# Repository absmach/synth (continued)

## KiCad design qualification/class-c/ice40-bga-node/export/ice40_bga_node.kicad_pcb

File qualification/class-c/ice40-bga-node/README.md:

# iCE40HX4K BGA node with a USB-C input and an MCU (Class C, case 1)

An iCE40HX4K FPGA in a 121-ball, 0.8 mm-pitch BGA with its supply chain, an SPI boot flash, one 12-pin header and four status LEDs, powered from a USB-C receptacle, with an STM32F103C8 companion MCU that programs the flash over USB, on six copper layers. It answers #328 under #40: a board with a BGA part, escaped under the pads, with via and fanout rules, made by an agent driving `synth mcp`.

## The board

| Group | Parts |
|---|---|
| Power entry | `J1` Korean Hroparts TYPE-C-31-M-12 USB-C receptacle (5 V from VBUS) with `R_CC1` and `R_CC2`, 5.1 k pull-downs on CC1 and CC2; `F1` Bourns MF-NSMF050-2 (0.5 A hold, 1 A trip, 13.2 V); `D1` Nexperia PTVS6V0S1UR (6.0 V standoff, 6.67 V minimum breakdown, 10.3 V clamp at 38.8 A); `Q1` Vishay SI2301CDS P-MOSFET reverse-polarity stage; `R3`, `C1` |
| USB data | `R25` and `R26`, 22 ohm series resistors in D+ and D- |
| MCU | `U5` STMicroelectronics STM32F103C8T6 (LQFP-48) on `+3V3_MCU`, which comes from `+3V3` through the ferrite bead `FB2`; supply decoupling `C27` to `C32` (five 100 nF and 4.7 uF); reset network `R21`, `C33` and the tactile switch `SW1`; `R22` pulls BOOT0 low; the crystal `Y1` with `C34` and `C35`; the 5-pin SWD header `J4` (3V3, SWDIO, SWCLK, NRST, GND) |
| 3.3 V | `U3` AMS1117-3.3 with 4 x 10 uF |
| 1.2 V core | `U4` Texas Instruments TLV70012DDCR, TSOT-23-5, with 1 uF in and 1 uF + 4.7 uF out; PLL supply `VCCPLL` through the ferrite bead `FB1` (Murata BLM18AG601SN1D) and `C20` to `C22` |
| FPGA | `U1` Lattice iCE40HX4K-BG121 (`VPP_FAST` unconnected), every supply ball decoupled |
| Configuration | `U2` Winbond W25Q128JVSIQ, SOIC-8 208 mil (5.3 mm body), master SPI; `CRESET_B` pulled up, `CDONE` with its LED |
| I/O | `J3` JXTCONN JXT-PZ2.54-1X12P-A1, 12 positions (3.3 V, ground and four FPGA I/O through 100 ohm series resistors) |
| Indicators and test points | four LEDs in one row, test points on 5 V, 3.3 V, 1.2 V, `CDONE` and `CRESET_B`, two M2.5 mounting holes at opposite corners (bottom left and top right) |

The MCU's job is to program the flash. `U5` streams the bitstream from the host over USB to `U2` over SPI1 (`PA4` to `PA7` to the flash's chip select, clock and data pins) and drives `CRESET_B` and `CDONE` from `PB0` and `PB1`. The iCE40HX4K bitstream is 135,183 bytes (1,081,464 bits) according to Lattice's iCE40 Programming and Configuration technical note FPGA-TN-02001-3.4, Table 9.2, which is more than the STM32F103C8's 64 KB of flash, so the 128 Mbit flash `U2` stays the bitstream store. The board carries no firmware.

The crystal `Y1` is the JYJE 3TJ480000FYLBC (LCSC `C2924620`): 8 MHz, load capacitance 8 pF, ESR 150 ohm maximum and C0 5 pF maximum, from the manufacturer's specification. The load capacitors are `C = 2 x (CL - Cstray) = 2 x (8 - 3) = 10 pF` each, with 3 pF of stray capacitance assumed. The start-up criterion `gm_crit = 4 x ESR x (2 pi f)^2 x (C0 + CL)^2` is 0.26 mA/V at the maximum ESR and C0.

The flash's package was checked against the manufacturer listings (LCSC, Arrow, RS, JITX): the W25Q128JVSIQ is an 8-pin SOIC of 208 mil, and the board's footprint is `Package_SO:SOIC-8_5.3x5.3mm_P1.27mm`. The TLV70012 is listed at LCSC only in the DDC (thin) package, which the board's footprint `TSOT-23-5` matches; its pinout is the same as the DBV package (1 IN, 2 GND, 3 EN, 4 NC, 5 OUT).

The qualification verdict, measurements, evidence and sign-off are in [`QUALIFICATION.md`](QUALIFICATION.md); how the board was made is in [`PROVENANCE.md`](PROVENANCE.md). Gerber content hash `ceeb7444dd`.

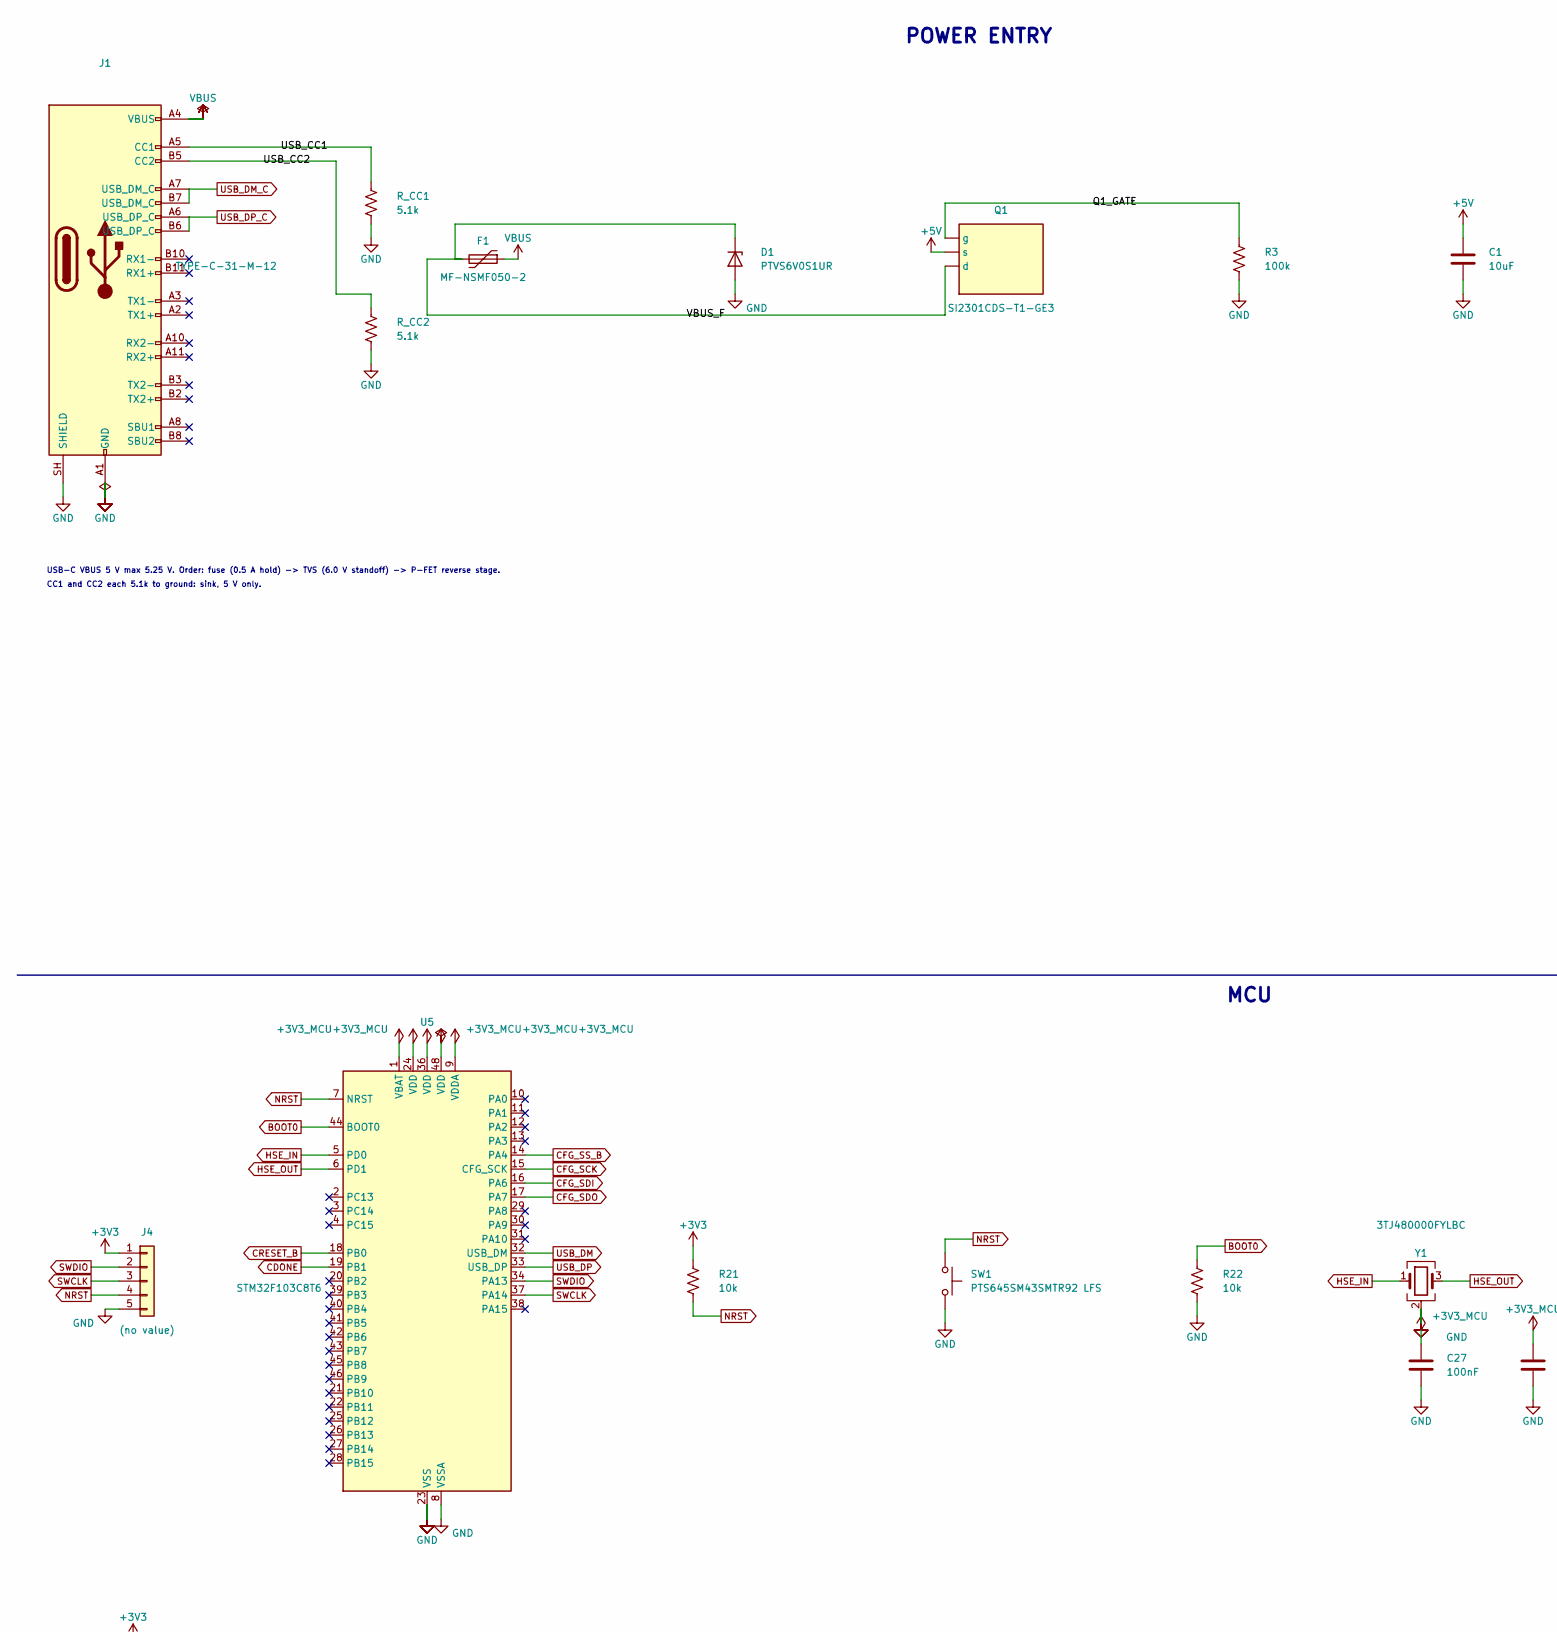
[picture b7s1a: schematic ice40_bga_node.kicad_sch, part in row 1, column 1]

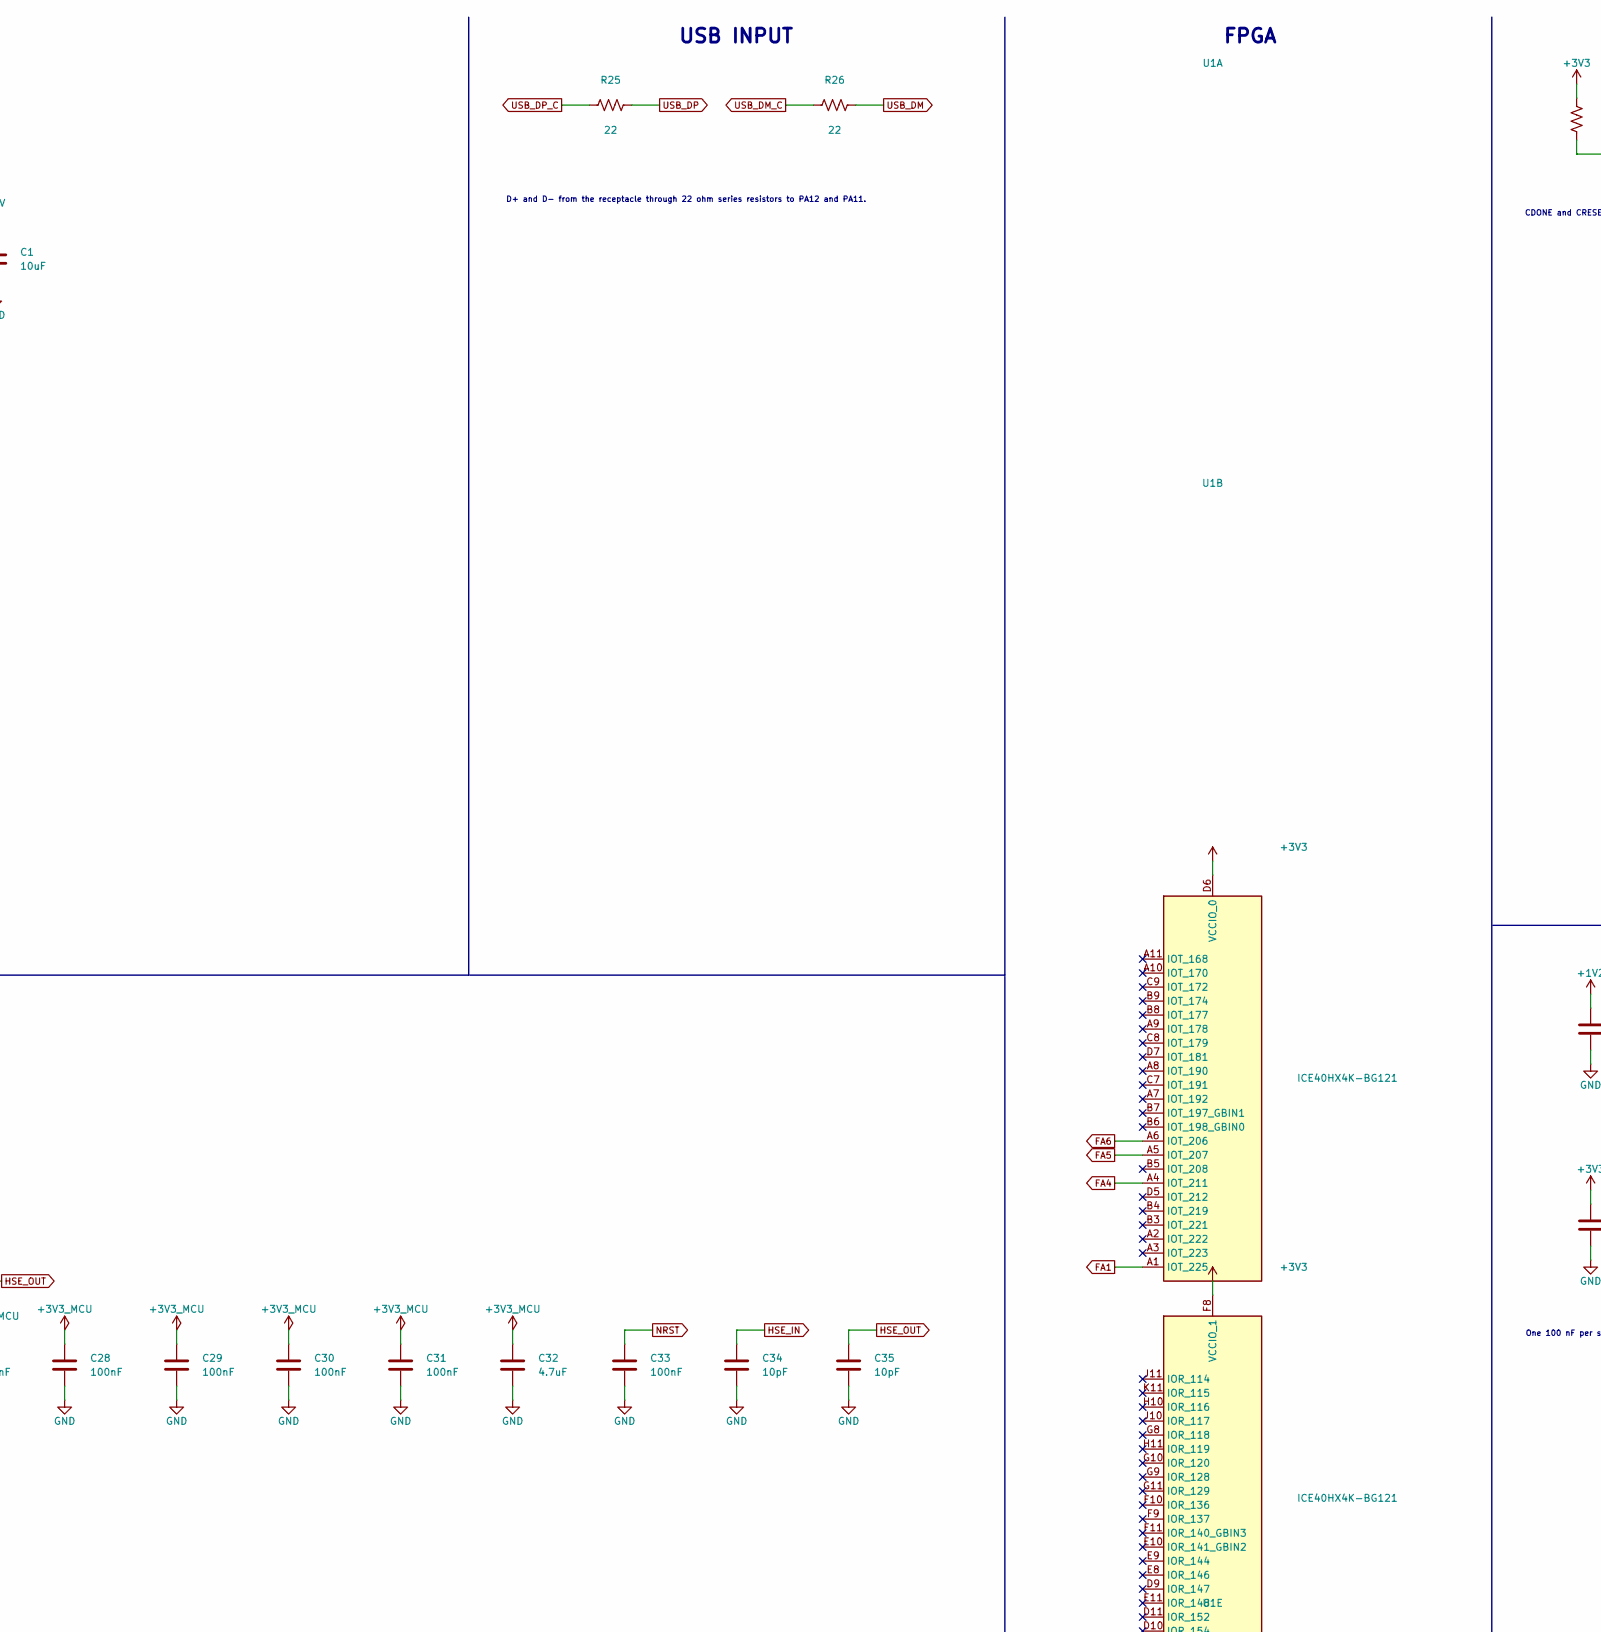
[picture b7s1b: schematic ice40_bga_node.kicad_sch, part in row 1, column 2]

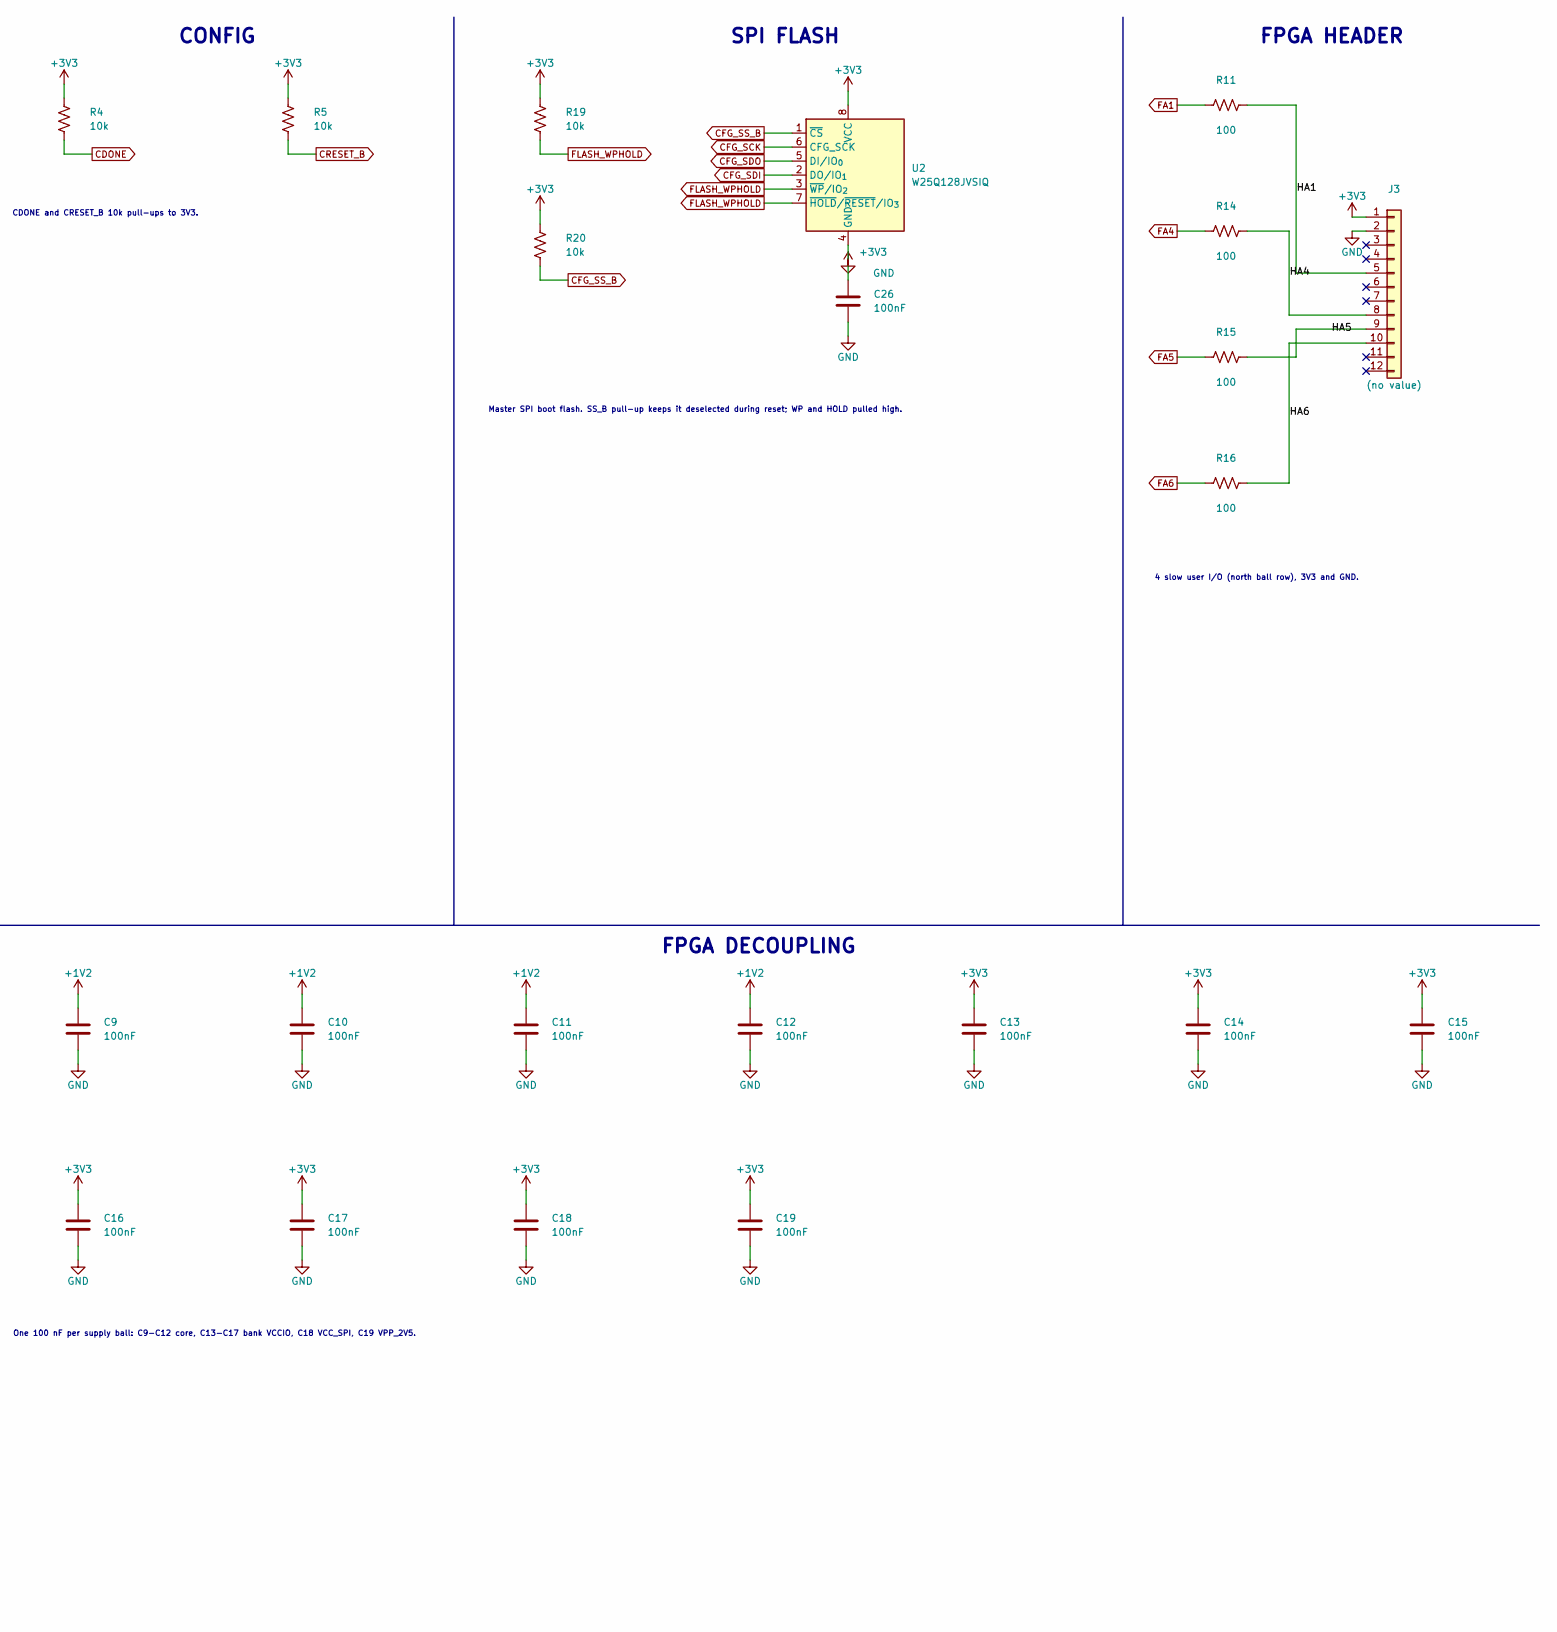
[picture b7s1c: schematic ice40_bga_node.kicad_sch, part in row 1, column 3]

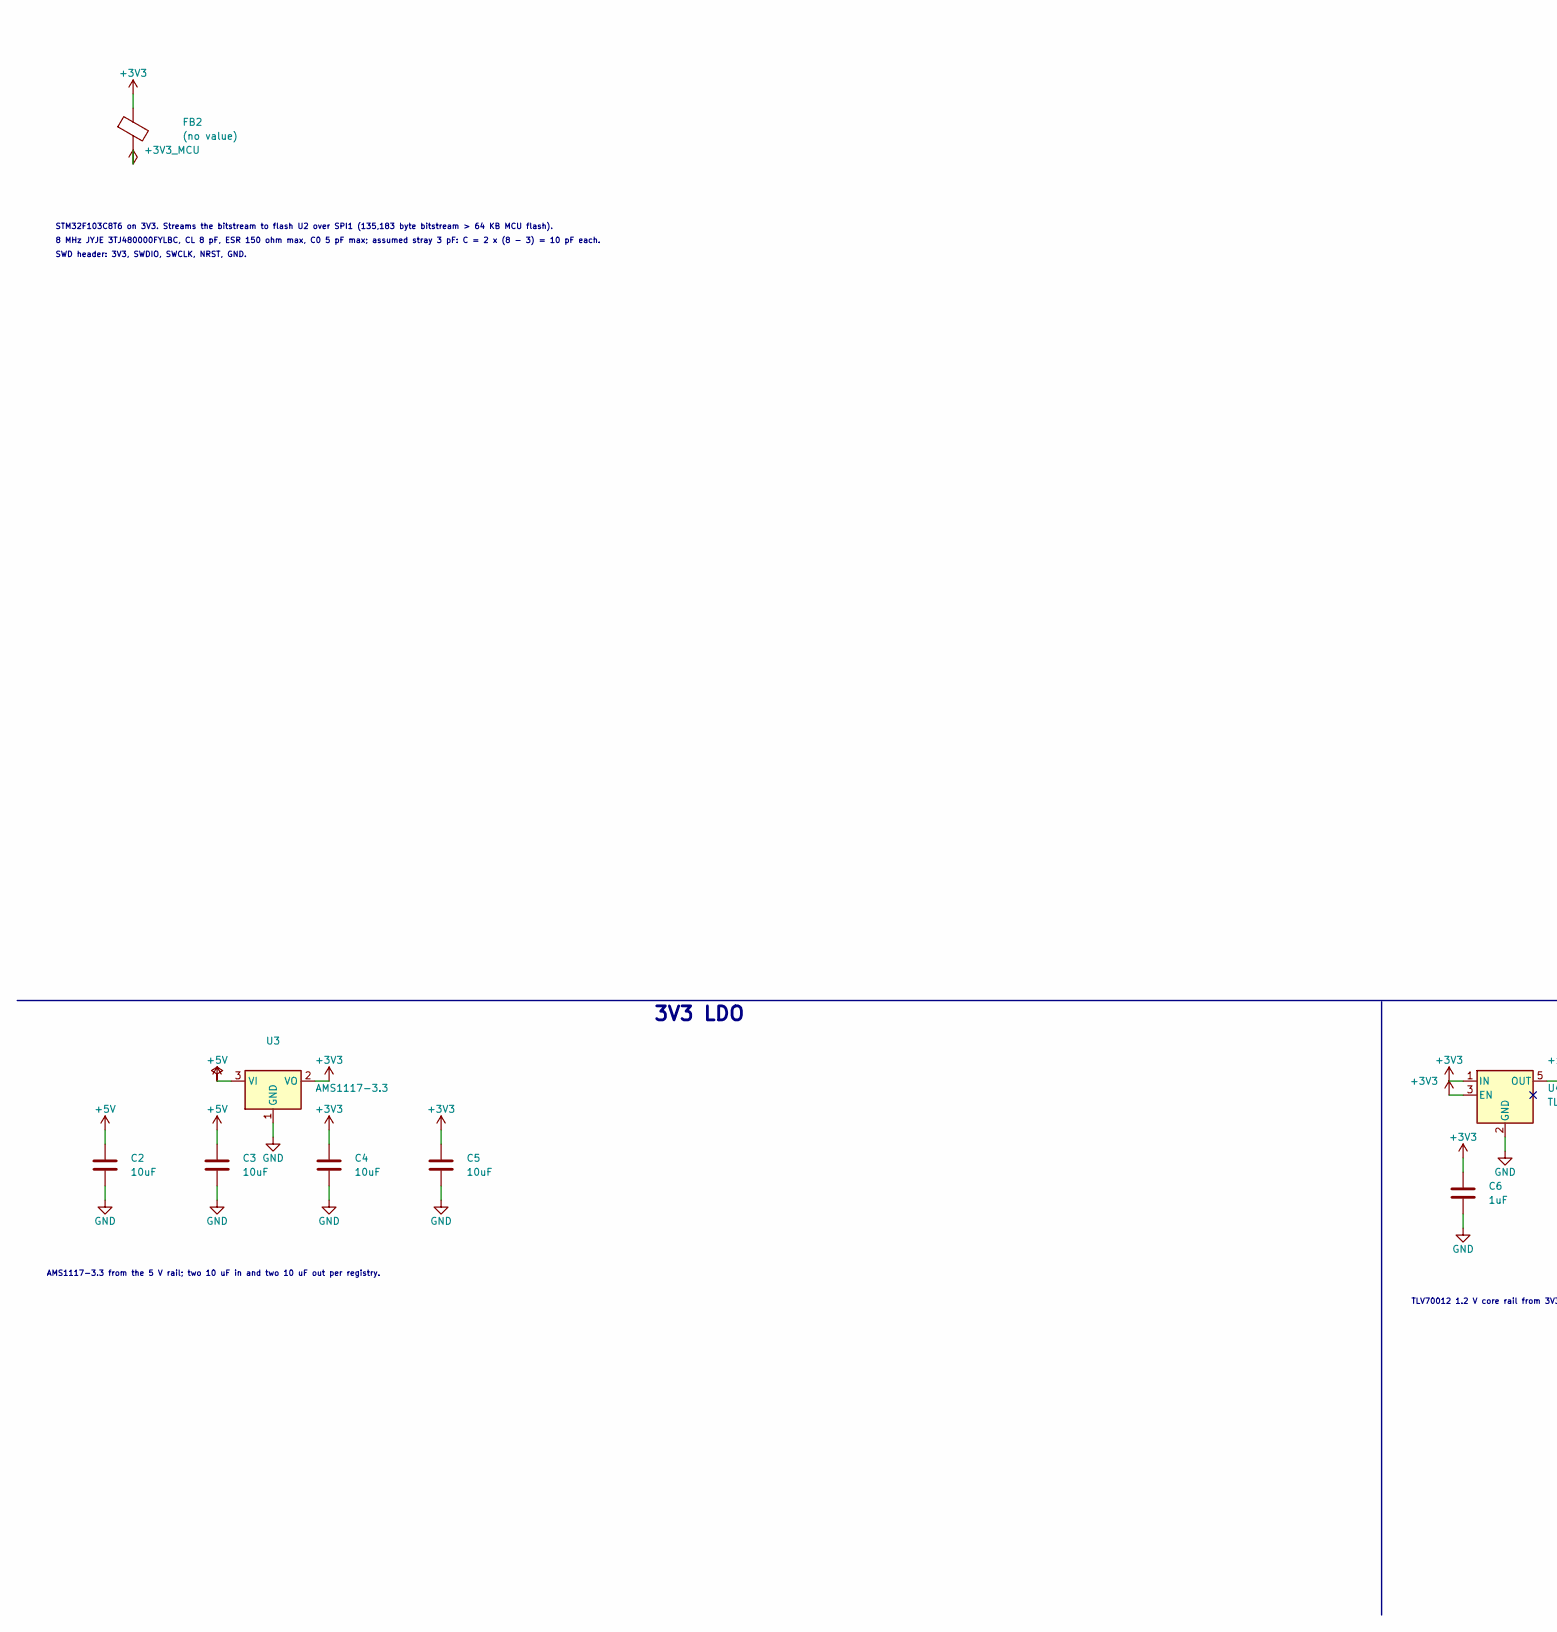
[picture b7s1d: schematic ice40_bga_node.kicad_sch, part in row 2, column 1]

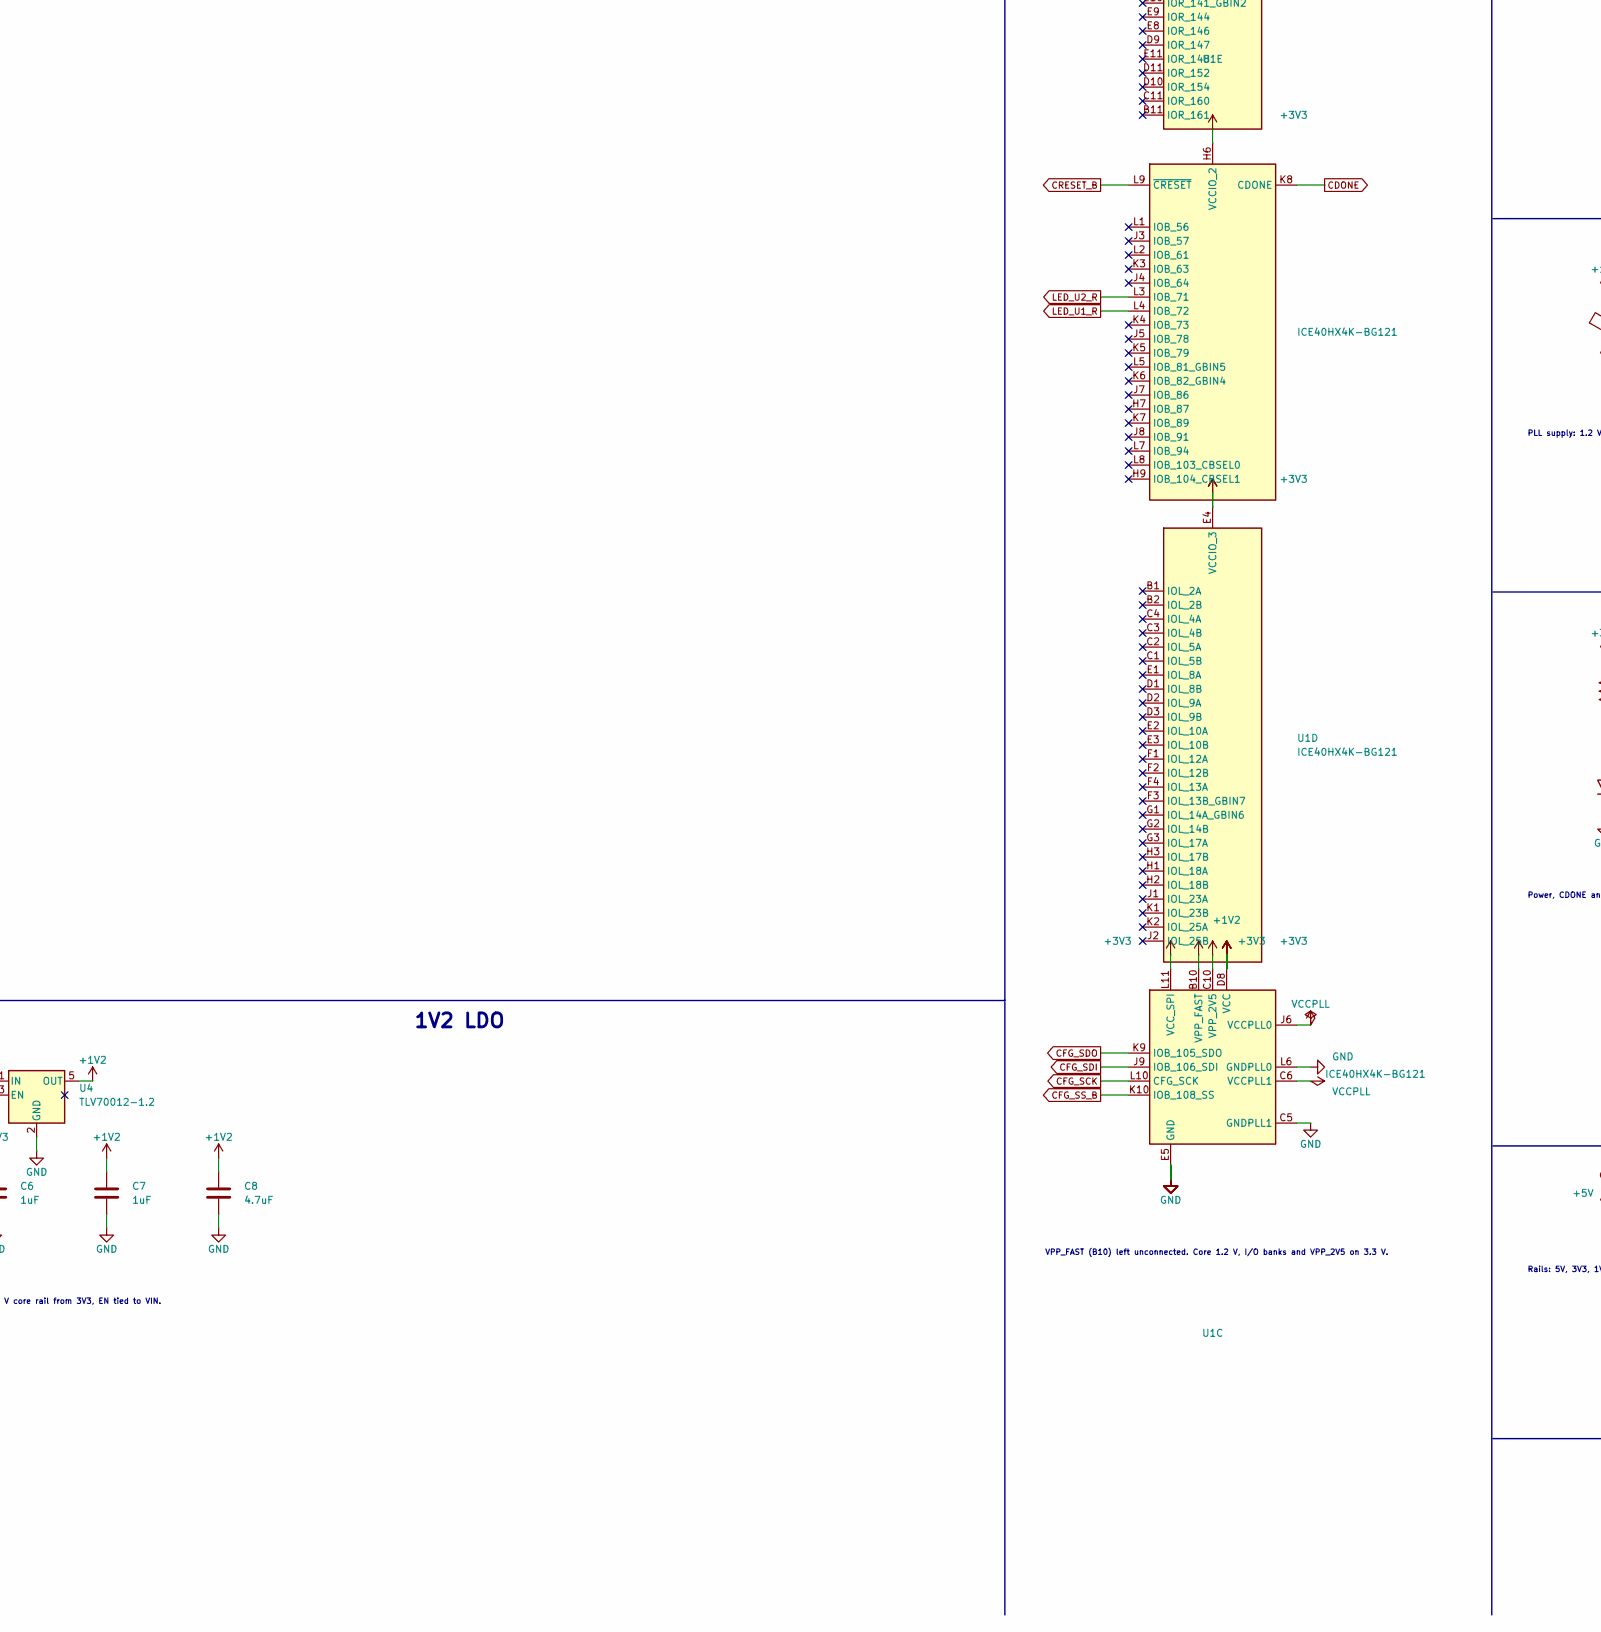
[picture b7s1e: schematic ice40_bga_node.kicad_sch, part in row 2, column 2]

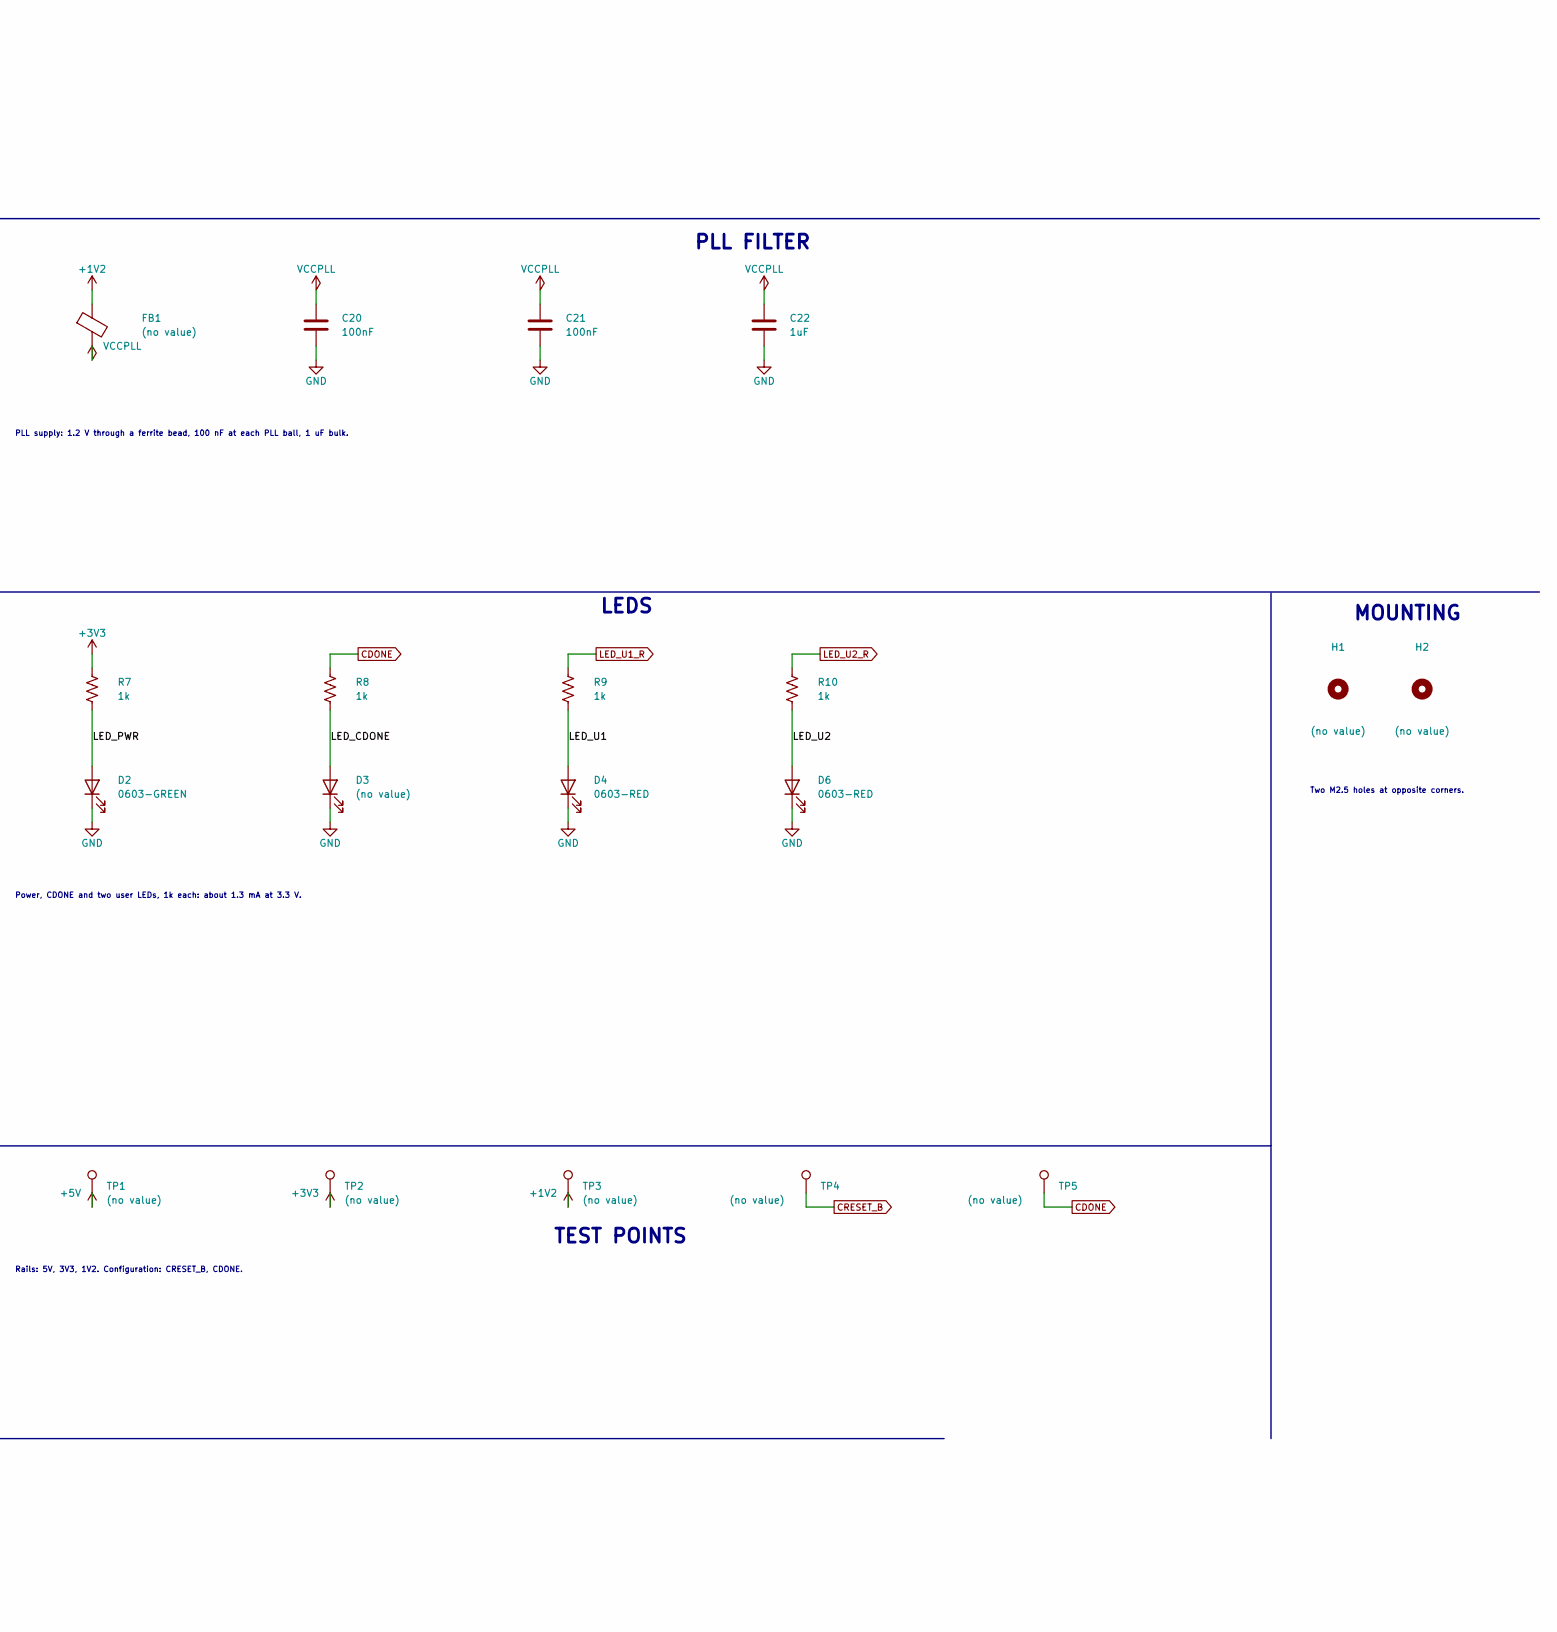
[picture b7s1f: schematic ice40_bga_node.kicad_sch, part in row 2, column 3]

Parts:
C1, C2, C3, C4, C5: 10uF; C_0805_2012Metric
C6, C7, C22: 1uF; C_0603_1608Metric
C8: 4.7uF; C_0805_2012Metric
C9, C10, C11, C12, C13, C14, C15, C16, C17, C18, C19, C20, C21, C26, C27, C28, C29, C30, C31, C33: 100nF; C_0402_1005Metric
C32: 4.7uF; C_0603_1608Metric
C34, C35: 10pF; C_0402_1005Metric
D1: PTVS6V0S1UR; Nexperia_CFP3_SOD-123W; MPN PTVS6V0S1UR
D2: 0603-GREEN; LED_0603_1608Metric; MPN 0603-GREEN; LCSC C72043
D3: (no value); LED_0603_1608Metric
D4, D6: 0603-RED; LED_0603_1608Metric; MPN 0603-RED; LCSC C2286
F1: MF-NSMF050-2; Fuse_1206_3216Metric; MPN MF-NSMF050-2; LCSC C75464
FB1, FB2: (no value); L_0603_1608Metric
H1, H2: (no value); MountingHole_2.5mm
J1: TYPE-C-31-M-12; USB_C_Receptacle_HRO_TYPE-C-31-M-12; MPN TYPE-C-31-M-12; LCSC C165948
J3: (no value); PinHeader_1x12_P2.54mm_Vertical
J4: (no value); PinHeader_1x05_P2.54mm_Vertical
Q1: SI2301CDS-T1-GE3; SOT-23; MPN SI2301CDS-T1-GE3; LCSC C10487
R3: 100k; R_0603_1608Metric
R4, R5, R19, R20, R21, R22: 10k; R_0402_1005Metric
R7, R8, R9, R10: 1k; R_0603_1608Metric
R11, R14, R15, R16: 100; R_0402_1005Metric
R25, R26: 22; R_0402_1005Metric
R_CC1, R_CC2: 5.1k; R_0402_1005Metric
SW1: PTS645SM43SMTR92 LFS; SW_SPST_PTS645Sx43SMTR92; MPN PTS645SM43SMTR92 LFS; LCSC C221880
TP1, TP2, TP3, TP4, TP5: (no value); TestPoint_Pad_D1.5mm
U1: ICE40HX4K-BG121; BGA-121_9.0x9.0mm_Layout11x11_P0.8mm_Ball0.4mm_Pad0.35mm_NS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; MPN ICE40HX4K-BG121
U2: W25Q128JVSIQ; SOIC-8_5.3x5.3mm_P1.27mm; MPN W25Q128JVSIQ; LCSC C97521
U3: AMS1117-3.3; SOT-223-3_TabPin2; MPN AMS1117-3.3; LCSC C6186
U4: TLV70012-1.2; TSOT-23-5; MPN TLV70012DDCR
U5: STM32F103C8T6; LQFP-48_7x7mm_P0.5mm; MPN STM32F103C8T6; LCSC C8734
Y1: 3TJ480000FYLBC; Crystal_SMD_3225-4Pin_3.2x2.5mm; MPN 3TJ480000FYLBC

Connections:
+1V2: C7.1, C8.1, C9.1, C10.1, C11.1, C12.1, FB1.1, TP3.1, U1.D4 (VCC), U1.D8 (VCC), U1.H4 (VCC), U1.H8 (VCC), U4.5 (OUT)
+3V3: C4.1, C5.1, C6.1, C13.1, C14.1, C15.1, C16.1, C17.1, C18.1, C19.1, C26.1, FB2.1, J3.1, J4.1, R4.1, R5.2, R7.1, R19.1, R20.1, R21.1, TP2.1, U1.B10 (VPP_FAST), U1.C10 (VPP_2V5), U1.D6 (VCCIO_0), U1.E4 (VCCIO_3), U1.F8 (VCCIO_1), U1.G4 (VCCIO_3), U1.H6 (VCCIO_2), U1.L11 (VCC_SPI), U2.8 (VCC), U3.2 (VO), U4.1 (IN), U4.3 (EN)
+3V3_MCU: C27.1, C28.1, C29.1, C30.1, C31.1, C32.1, FB2.2, U5.1 (VBAT), U5.9 (VDDA), U5.24 (VDD), U5.36 (VDD), U5.48 (VDD)
+5V: C1.1, C2.1, C3.1, Q1.2 (s), TP1.1, U3.3 (VI)
BOOT0: R22.1, U5.44 (BOOT0)
CDONE: R4.2, R8.1, TP5.1, U1.K8 (CDONE), U5.19 (PB1)
CFG_SCK: U1.L10 (IOB_107_SCK), U2.6 (CLK), U5.15 (PA5)
CFG_SDI: U1.J9 (IOB_106_SDI), U2.2 (DO/IO_{1}), U5.16 (PA6)
CFG_SDO: U1.K9 (IOB_105_SDO), U2.5 (DI/IO_{0}), U5.17 (PA7)
CFG_SS_B: R20.2, U1.K10 (IOB_108_SS), U2.1 (~CS), U5.14 (PA4)
CRESET_B: R5.1, TP4.1, U1.L9 (~CRESET), U5.18 (PB0)
FA1: R11.1, U1.A1 (IOT_225), U1.B1 (IOL_2A)
FA4: R14.1, U1.A4 (IOT_211), U1.A9 (IOT_178), U1.B4 (IOT_219), U1.B9 (IOT_174)
FA5: R15.1, U1.A5 (IOT_207)
FA6: R16.1, U1.A6 (IOT_206), U1.B6 (IOT_198_GBIN0)
FLASH_WPHOLD: R19.2, U2.3 (~WP/IO_{2}), U2.7 (~HOLD/~RESET/IO_{3})
GND: C1.2, C2.2, C3.2, C4.2, C5.2, C6.2, C7.2, C8.2, C9.2, C10.2, C11.2, C12.2, C13.2, C14.2, C15.2, C16.2, C17.2, C18.2, C19.2, C20.2, C21.2, C22.2, C26.2, C27.2, C28.2, C29.2, C30.2, C31.2, C32.2, C33.2, C34.2, C35.2, D1.2 (A), D2.1 (K), D3.1 (K), D4.1 (K), D6.1 (K), J1.A1 (GND), J1.A12 (GND), J1.B1 (GND), J1.B12 (GND), J1.SH (SHIELD), J3.2, J4.5, R3.2, R22.2, R_CC1.2, R_CC2.2, SW1.2, U1.C5 (GNDPLL1), U1.E5 (GND), U1.E6 (GND), U1.E7 (GND), U1.F5 (GND), U1.F6 (GND), U1.F7 (GND), U1.G5 (GND), U1.G6 (GND), U1.G7 (GND), U1.H5 (GND), U1.L6 (GNDPLL0), U2.4 (GND), U3.1 (GND), U4.2 (GND), U5.8 (VSSA), U5.23 (VSS), U5.35 (VSS), U5.47 (VSS), Y1.2 (G), Y1.4 (G)
HA1: J3.5, R11.2
HA4: J3.8, R14.2
HA5: J3.9, R15.2
HA6: J3.10, R16.2
HSE_IN: C34.1, U5.5 (PD0), Y1.1
HSE_OUT: C35.1, U5.6 (PD1), Y1.3
LED_CDONE: D3.2 (A), R8.2
LED_PWR: D2.2 (A), R7.2
LED_U1: D4.2 (A), R9.2
LED_U1_R: R9.1, U1.L4 (IOB_72)
LED_U2: D6.2 (A), R10.2
LED_U2_R: R10.1, U1.L3 (IOB_71)
NRST: C33.1, J4.4, R21.2, SW1.1, U5.7 (NRST)
Q1_GATE: Q1.1 (g), R3.1
SWCLK: J4.3, U5.37 (PA14)
SWDIO: J4.2, U5.34 (PA13)
USB_CC1: J1.A5 (CC1), R_CC1.1
USB_CC2: J1.B5 (CC2), R_CC2.1
USB_DM: R26.2, U5.32 (PA11)
USB_DM_C: J1.A7 (D-), J1.B7 (D-), R26.1
USB_DP: R25.2, U5.33 (PA12)
USB_DP_C: J1.A6 (D+), J1.B6 (D+), R25.1
VBUS: F1.1, J1.A4 (VBUS), J1.A9 (VBUS), J1.B4 (VBUS), J1.B9 (VBUS)
VBUS_F: D1.1 (K), F1.2, Q1.3 (d)
VCCPLL: C20.1, C21.1, C22.1, FB1.2, U1.C6 (VCCPLL1), U1.J6 (VCCPLL0)

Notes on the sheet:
POWER ENTRY
USB INPUT
MCU
3V3 LDO
1V2 LDO
FPGA
FPGA DECOUPLING
PLL FILTER
CONFIG
SPI FLASH
LEDS
FPGA HEADER
TEST POINTS
MOUNTING
USB-C VBUS 5 V max 5.25 V. Order: fuse (0.5 A hold) -> TVS (6.0 V standoff) -> P-FET reverse stage.
CC1 and CC2 each 5.1k to ground: sink, 5 V only.
D+ and D- from the receptacle through 22 ohm series resistors to PA12 and PA11.
STM32F103C8T6 on 3V3. Streams the bitstream to flash U2 over SPI1 (135,183 byte bitstream > 64 KB MCU flash).
8 MHz JYJE 3TJ480000FYLBC, CL 8 pF, ESR 150 ohm max, C0 5 pF max; assumed stray 3 pF: C = 2 x (8 - 3) = 10 pF each.
SWD header: 3V3, SWDIO, SWCLK, NRST, GND.
AMS1117-3.3 from the 5 V rail; two 10 uF in and two 10 uF out per registry.
TLV70012 1.2 V core rail from 3V3, EN tied to VIN.
VPP_FAST (B10) left unconnected. Core 1.2 V, I/O banks and VPP_2V5 on 3.3 V.
One 100 nF per supply ball: C9-C12 core, C13-C17 bank VCCIO, C18 VCC_SPI, C19 VPP_2V5.
PLL supply: 1.2 V through a ferrite bead, 100 nF at each PLL ball, 1 uF bulk.
CDONE and CRESET_B 10k pull-ups to 3V3.
Master SPI boot flash. SS_B pull-up keeps it deselected during reset; WP and HOLD pulled high.
Power, CDONE and two user LEDs, 1k each: about 1.3 mA at 3.3 V.
4 slow user I/O (north ball row), 3V3 and GND.
Rails: 5V, 3V3, 1V2. Configuration: CRESET_B, CDONE.
Two M2.5 holes at opposite corners.
